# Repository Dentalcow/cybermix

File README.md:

# Cybermix
An application volume mixer with a vague cyberpunk theme. 5 faders, 5 screens, and a desktop companion app. It supports pages and any app that you what to control the volume of in WINDOWS (as of now).

### Concept
The concept is a physical hardware version of the windows volume mixer, but reimagined with a cyberpunk look and more customisation.

### The Software
A custom developed software which allows the control and assignment of apps to faders on the device. 

### The Hardware
A custom PCB with hidden messaging.

Schematic:

### Bill of Materials for electronics (Quantity may be inaccurate due to batch pricing on Aliexpress; See notes)

| Item                                   | Cost | Req Quantity | Total Cost | Link                                                                                                    | Notes                                             |
|----------------------------------------|------|--------------|------------|---------------------------------------------------------------------------------------------------------|---------------------------------------------------|
| Custom PCB                             | 13.6 | 1            | 13.6       | Any pcb manufacturer (I used JLCPCB)                                                                    |                                                   |
| Seeed Studio RP2040 XIAO               | 4.68 | 1            | 4.68       | https://www.digikey.com.au/en/products/detail/seeed-technology-co-ltd/102010428/14672129               |                                                   |
| ADS1115                                | 2.17 | 1            | 2.17       | https://www.aliexpress.com/item/1005006349857176.html                                                   | You need 10; aliexpress sells in batches of 20    |
| SK6812 Mini-e RGB                      | 2.07 | 1            | 2.07       | https://www.aliexpress.com/item/1005005193716172.html                                                   |                                                   |
| PTA-6043                               | 1.92 | 1            | 1.92       | https://www.digikey.com.au/en/products/detail/bourns-inc/PTA6043-2015CPB103/3781230                     |                                                   |
| SSD1306 Yellow and Blue 128x64 OLED    | 7.47 | 1            | 7.47       | https://www.aliexpress.com/item/1005008738379315.html                                                   | You need 5; aliexpress sells in batches of 5      |
| TCA9848A                                | 2.03 | 1            | 2.03       | https://www.aliexpress.com/item/1005004996004241.html                                                   |                                                   |
| MX style key switches                  | 4.76 | 1            | 4.76       | https://www.aliexpress.com/item/1005010149555052.html                                                   | You need 2; aliexpress sells in batches of 10     |
| 1x40 pin header                         | 1.44 | 1            | 1.44       | https://www.aliexpress.com/item/1005007385580884.html                                                   | Break into 16 pin and 4 pin headers               |
| Total                                  |      |              | 40.41      |                                                                                                         |                                                   |

### Bill of Materials for hardware

| Item               | Cost | Req Quantity | Total Cost | Link                                                                                  | Notes                                                |
|--------------------|------|--------------|------------|---------------------------------------------------------------------------------------|------------------------------------------------------|
| M3 Heatset Inserts | 6.89 | 1            | 6.89       | https://www.aliexpress.com/item/1005009646586344.html                                | You need 8 but they are sold in sets of 100          |
| M3 Screws          | 1.32 | 1            | 1.32       | https://www.aliexpress.com/item/1005004527586307.html                                | You need 8 but they are sold in sets of 40           |
| USB C 1m Cable     | 2.79 | 1            | 2.79       | https://www.aliexpress.com/item/1005007431063094.html                                |                                                      |
| Total              |      |              | 11         |                                                                                       |                                                      |

### Showcase

COMING SOON

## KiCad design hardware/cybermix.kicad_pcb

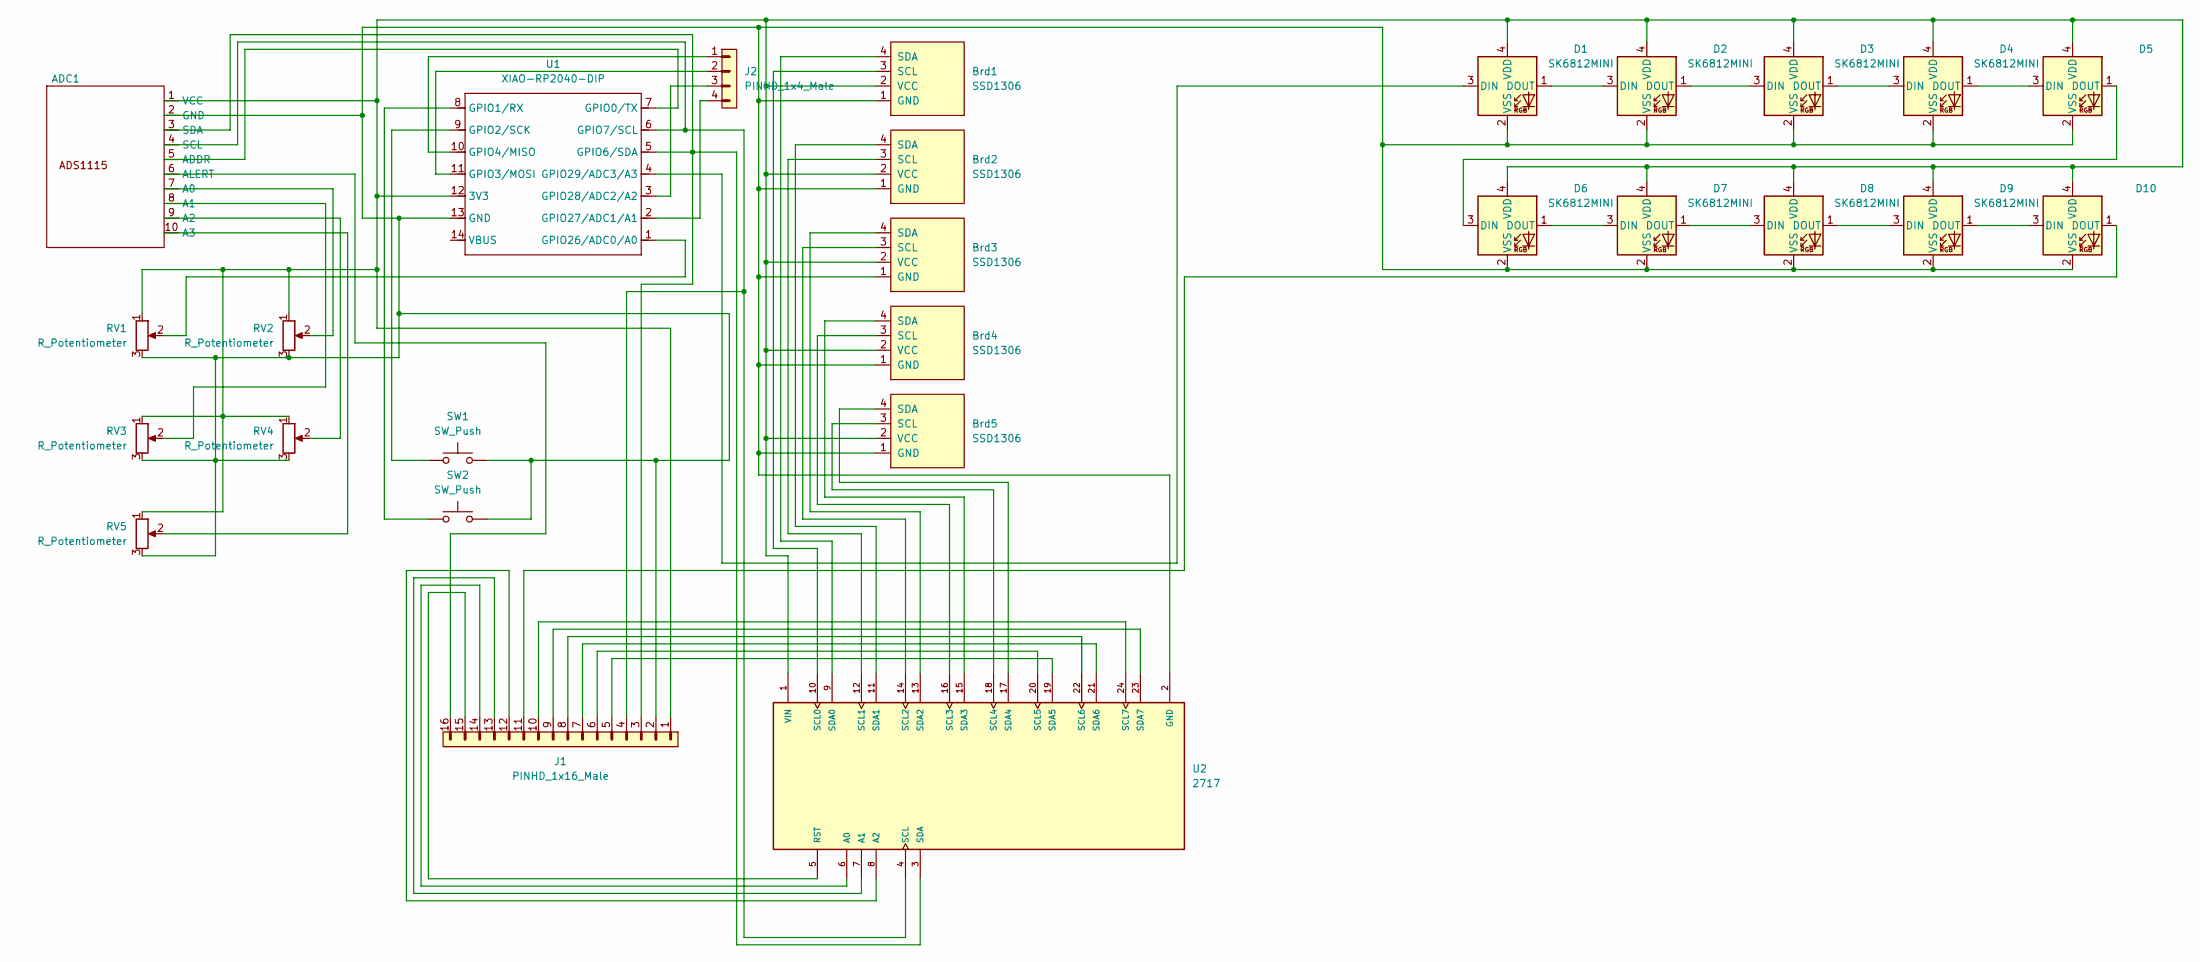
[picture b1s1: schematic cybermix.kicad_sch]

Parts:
ADC1: PinHeader_1x10_P1.00mm_Vertical
Brd1, Brd2, Brd3, Brd4, Brd5: SSD1306; 128x64OLED
D1, D2, D3, D4, D5, D6, D7, D8, D9, D10: SK6812MINI; LED_SK6812MINI_PLCC4_3.5x3.5mm_P1.75mm
J1: PINHD_1x16_Male; PinHeader_1x16_P2.54mm_Vertical
J2: PINHD_1x4_Male; PinHeader_1x04_P2.54mm_Vertical
RV1, RV2, RV3, RV4, RV5: R_Potentiometer; TRIM_PTA6043-2015CPB103
SW1, SW2: SW_Push; SW_Cherry_MX_1.00u_PCB
U1: XIAO-RP2040-DIP; MOUDLE14P-XIAO-DIP-SMD
U2: 2717; MODULE_2717; PARTREV Sep 11, 2015

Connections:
unnamed: ADC1.7 (A0), RV2.2
unnamed: ADC1.8 (A1), RV3.2
unnamed: ADC1.9 (A2), RV4.2
unnamed: ADC1.10 (A3), RV5.2
unnamed: ADC1.5 (ADDR), U1.7 (GPIO0/TX)
unnamed: ADC1.6 (ALERT), J1.16
unnamed: ADC1.2 (GND), Brd1.1 (GND), Brd2.1 (GND), Brd3.1 (GND), Brd4.1 (GND), Brd5.1 (GND), D1.2 (VSS), D2.2 (VSS), D3.2 (VSS), D4.2 (VSS), D5.2 (VSS), D6.2 (VSS), D7.2 (VSS), D8.2 (VSS), D9.2 (VSS), D10.2 (VSS), J1.2, RV1.3, RV2.3, RV3.3, RV4.3, RV5.3, SW1.2, SW2.2, U1.13 (GND), U2.2 (GND)
unnamed: ADC1.4 (SCL), J1.4, U1.6 (GPIO7/SCL), U2.4 (SCL)
unnamed: ADC1.3 (SDA), J1.3, U1.5 (GPIO6/SDA), U2.3 (SDA)
unnamed: ADC1.1 (VCC), Brd1.2 (VCC), Brd2.2 (VCC), Brd3.2 (VCC), Brd4.2 (VCC), Brd5.2 (VCC), D1.4 (VDD), D2.4 (VDD), D3.4 (VDD), D4.4 (VDD), D5.4 (VDD), D6.4 (VDD), D7.4 (VDD), D8.4 (VDD), D9.4 (VDD), D10.4 (VDD), J1.1, RV1.1, RV2.1, RV3.1, RV4.1, RV5.1, U1.12 (3V3), U2.1 (VIN)
unnamed: Brd1.3 (SCL), U2.10 (SCL0)
unnamed: Brd1.4 (SDA), U2.9 (SDA0)
unnamed: Brd2.3 (SCL), U2.12 (SCL1)
unnamed: Brd2.4 (SDA), U2.11 (SDA1)
unnamed: Brd3.3 (SCL), U2.14 (SCL2)
unnamed: Brd3.4 (SDA), U2.13 (SDA2)
unnamed: Brd4.3 (SCL), U2.16 (SCL3)
unnamed: Brd4.4 (SDA), U2.15 (SDA3)
unnamed: Brd5.3 (SCL), U2.18 (SCL4)
unnamed: Brd5.4 (SDA), U2.17 (SDA4)
unnamed: D1.3 (DIN), U1.4 (GPIO29/ADC3/A3)
unnamed: D1.1 (DOUT), D2.3 (DIN)
unnamed: D2.1 (DOUT), D3.3 (DIN)
unnamed: D3.1 (DOUT), D4.3 (DIN)
unnamed: D4.1 (DOUT), D5.3 (DIN)
unnamed: D5.1 (DOUT), D6.3 (DIN)
unnamed: D6.1 (DOUT), D7.3 (DIN)
unnamed: D7.1 (DOUT), D8.3 (DIN)
unnamed: D8.1 (DOUT), D9.3 (DIN)
unnamed: D9.1 (DOUT), D10.3 (DIN)
unnamed: D10.1 (DOUT), J1.11
unnamed: SW2.1, U1.8 (GPIO1/RX)
unnamed: SW1.1, U1.9 (GPIO2/SCK)
unnamed: J2.2, U1.11 (GPIO3/MOSI)
unnamed: J2.1, U1.10 (GPIO4/MISO)
unnamed: RV1.2, U1.1 (GPIO26/ADC0/A0)
unnamed: J2.4, U1.2 (GPIO27/ADC1/A1)
unnamed: J2.3, U1.3 (GPIO28/ADC2/A2)
unnamed: J1.14, U2.6 (A0)
unnamed: J1.13, U2.7 (A1)
unnamed: J1.12, U2.8 (A2)
unnamed: J1.15, U2.5 (RST)
unnamed: J1.6, U2.20 (SCL5)
unnamed: J1.8, U2.22 (SCL6)
unnamed: J1.10, U2.24 (SCL7)
unnamed: J1.5, U2.19 (SDA5)
unnamed: J1.7, U2.21 (SDA6)
unnamed: J1.9, U2.23 (SDA7)

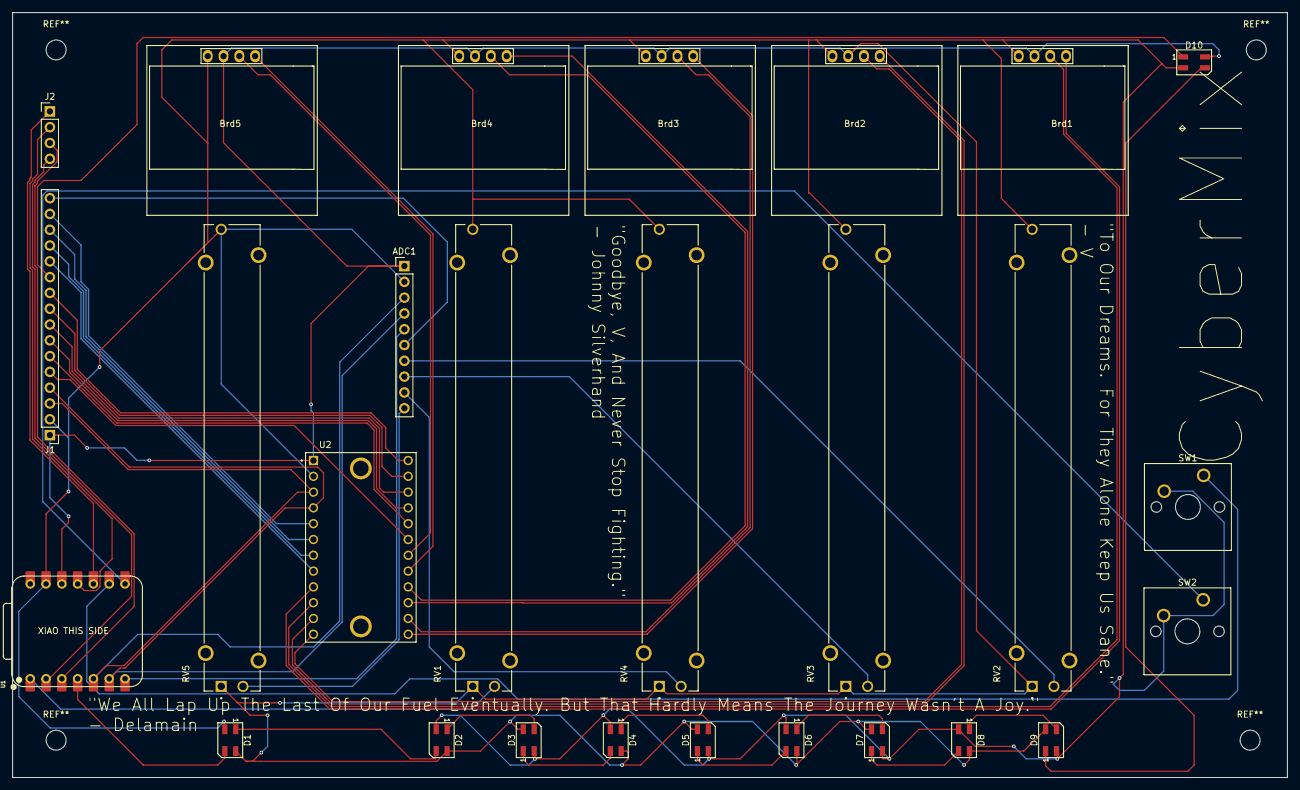
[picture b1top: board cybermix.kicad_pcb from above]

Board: 2 copper layers, 205.0 x 123.0 mm, 27 parts (0 on the bottom side), 48 nets.

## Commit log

2025-12-03 Update README with product links
    Added links to Texas Instruments and Seeed Studio products.
2025-12-03 Add AliExpress link to README
2025-12-03 Clean up README by removing links
    Removed unnecessary links from README.
2025-12-03 Add additional product links to README
2025-12-03 Add new Aliexpress link to README
2025-12-03 Add product link to Aliexpress
    Add additional product link to README
2025-12-04 Add Bill of Materials to README
    Added a Bill of Materials section with item details and links.
2025-12-04 Revise Bill of Materials with updated costs and links
    Updated item costs and links in the Bill of Materials.
2025-12-04 Clarify Bill of Materials section in README
2025-12-04 Add render image to README
    Added a render image to the README for visual reference.
2025-12-04 Revise Bill of Materials with item details and links
    Updated the Bill of Materials section with detailed item information and links.
2025-12-04 Fix capitalization in project title
2025-12-04 Initial plan
2025-12-04 Add CyberMix desktop app and firmware sources
    Introduces initial implementation of the CyberMix desktop controller (cybermix_desktop.py), a PyQt5 GUI (cybermix_gui.py), and a MicroPython firmware baseline (main.py) for Seeed XIAO RP2040. Include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
2025-12-05 Enhance README with detailed application info
    Expanded description of the Cybermix application and provided details about the software and hardware components.
2025-12-05 Update README to include Showcase section
    Added a new section for the Showcase and removed the Render section.
2025-12-05 Update code (Small bug fixes)
2025-12-05 Add CAD files and BOM files
2025-12-05 Update README with project description and images
2025-12-05 Update PCB cost in the Bill of Materials
2025-12-05 update files
